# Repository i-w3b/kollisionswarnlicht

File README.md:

### kollisionswarnlicht

| Part   | Datenblatt | Preis |
|:---------------:|:---------------:|:---------------:|
|[Controller(Atmega32U4AU)](https://www.digikey.de/product-detail/de/microchip-technology/ATMEGA32U4-AU/ATMEGA32U4-AU-ND/1914602)| [Datenblatt](https://ww1.microchip.com/downloads/en/DeviceDoc/Atmel-7766-8-bit-AVR-ATmega16U4-32U4_Datasheet.pdf)  | €3,81 |
| [USB-Anschluss](https://www.digikey.de/product-detail/de/gct/USB3075-30-A/2073-USB3075-30-ACT-ND/9859705)| - | €0,55 | 
| [RJ12-Anschluss](https://www.digikey.de/product-detail/de/pulse-electronics-network/E5566-Q0LK22-L/553-2258-ND/1785239) | - | €0,45 |
| [Quartz - Alt](https://www.digikey.de/product-detail/de/txc-corporation/7A-16.000MAAJ-T/887-1086-2-ND/2118770) | - | €0,31 |
| [Quartz](https://www.digikey.de/product-detail/de/epson/FA-238-16-0000MB-C3/SER3686CT-ND/2403459) | - | €0,27 |
| [LED](https://www.digikey.de/product-detail/de/cree-inc/XHP50A-00-0000-0D0BJ40E2/XHP50A-00-0000-0D0BJ40E2TR-ND/5303071) | [Datenblatt](https://cree-led.com/media/documents/ds-XHP50.pdf) | €4,53 |
| [LED-Treiber](https://www.digikey.de/product-detail/de/leddynamics-inc/3021-D-E-1000/788-1107-ND/3114438) | [Datenblatt](http://www.leddynamics.com/wp-content/uploads/2018/11/03021_03023_BuckPuck_v3-1.pdf)| €7,83 |
| [PNP-Transistor](https://www.digikey.de/product-detail/de/taiwan-semiconductor-corporation/MMBT3906-RFG/MMBT3906RFGCT-ND/7644317) | [Datenblatt](https://www.taiwansemi.com/assets/uploads/datasheet/MMBT3906_H2001.pdf) | €0,03 |
| [Load-Switch](https://www.digikey.de/product-detail/de/infineon-technologies/BTS71202EPAXUMA1/BTS71202EPAXUMA1CT-ND/9906589) | [Datenblatt](https://www.infineon.com/dgdl/Infineon-BTS7120-2EPA-DS-v01_00-EN.pdf?fileId=5546d462636cc8fb016421dc08d31138) | 1,41€ |
| [220uF Kondensator](https://www.digikey.de/products/de?keywords=P124108CT-ND) | [Datenblatt](https://industrial.panasonic.com/cdbs/www-data/pdf/RDD0000/RDD0000C1244.pdf) |2,61€ |
| [Poti](https://www.digikey.de/product-detail/de/nidec-copal-electronics/ST32ETA502/ST32ETA502CT-ND/738477) | [Datenblatt](https://www.nidec-copal-electronics.com/e/catalog/trimmer/st-32.pdf) | 1,09€ |

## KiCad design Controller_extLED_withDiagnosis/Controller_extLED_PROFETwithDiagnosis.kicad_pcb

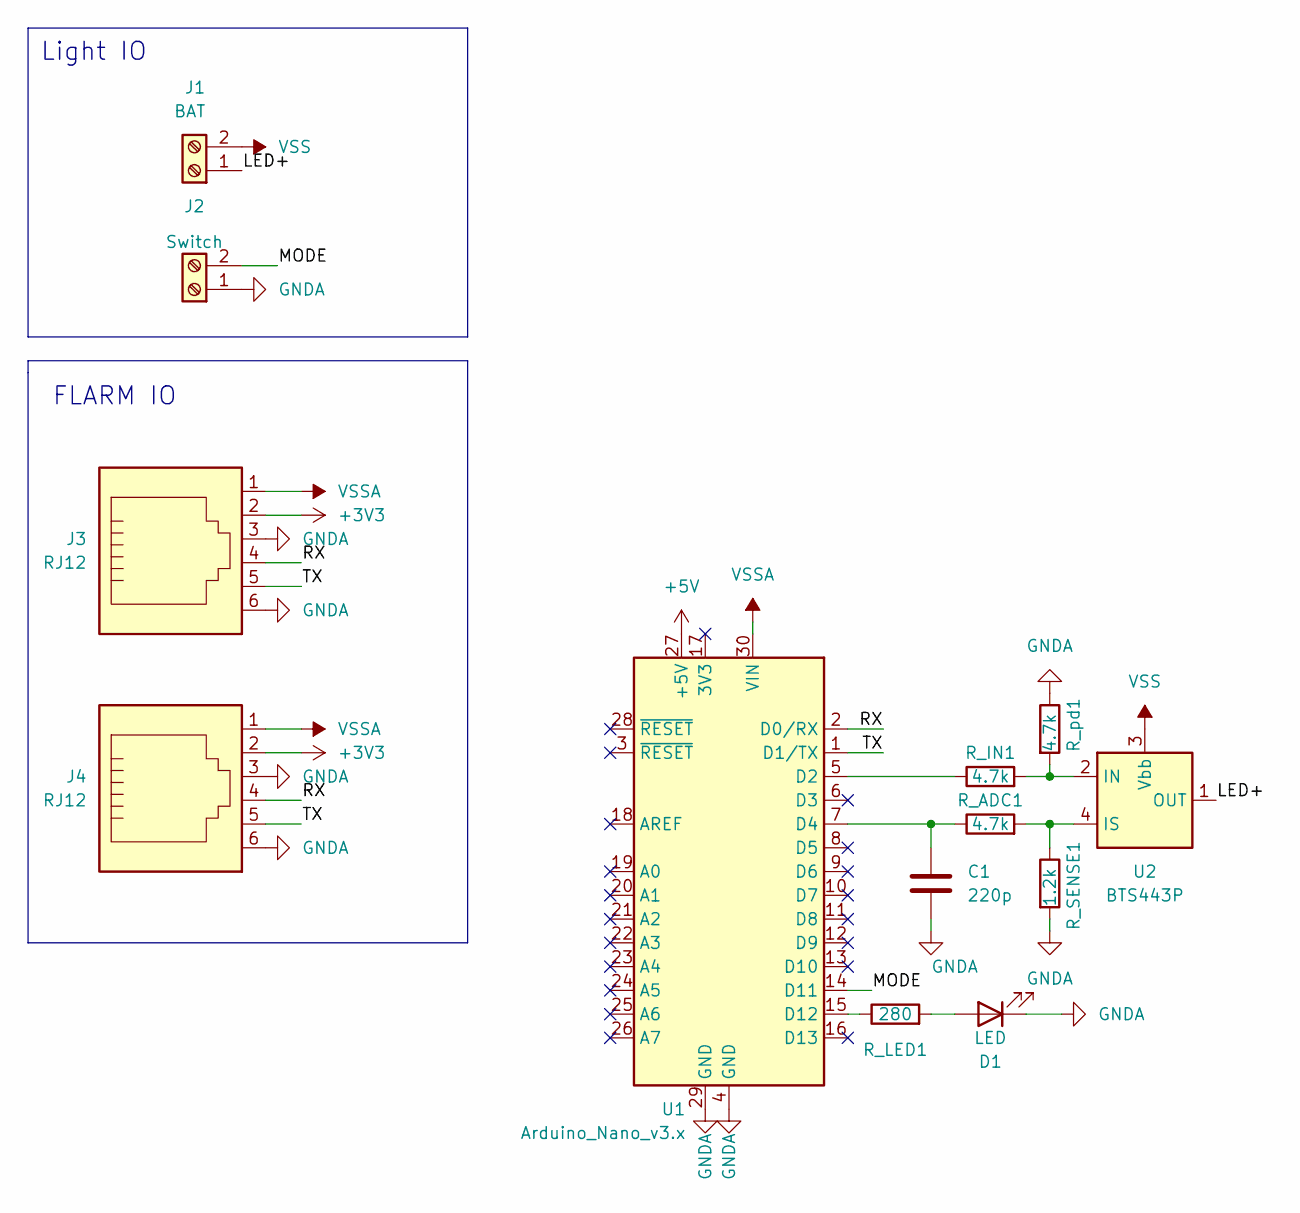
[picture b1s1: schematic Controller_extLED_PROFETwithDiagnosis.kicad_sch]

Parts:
C1: 220p; C_0805_2012Metric_Pad1.18x1.45mm_HandSolder
D1: LED; LED_D3.0mm
J1: BAT; TerminalBlock_bornier-2_P5.08mm
J2: Switch; TerminalBlock_TE_282834-2_1x02_P2.54mm_Horizontal
J3, J4: RJ12; RJ12_Amphenol_54601
R_ADC1: 4.7k; R_0805_2012Metric_Pad1.20x1.40mm_HandSolder
R_IN1: 4.7k; R_0805_2012Metric_Pad1.20x1.40mm_HandSolder
R_LED1: 280; R_0805_2012Metric_Pad1.20x1.40mm_HandSolder
R_SENSE1: 1.2k; R_0805_2012Metric_Pad1.20x1.40mm_HandSolder
R_pd1: 4.7k; R_0805_2012Metric_Pad1.20x1.40mm_HandSolder
U1: Arduino_Nano_v3.x; Arduino_Nano
U2: BTS443P; TO-252-4

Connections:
+3V3: J3.2, J4.2
+5V: U1.27 (+5V)
/LED+: J1.1, U2.1 (OUT), U2.5 (OUT)
/MODE: J2.2, U1.14 (D11)
/RX: J3.4, J4.4, U1.2 (D0/RX)
/TX: J3.5, J4.5, U1.1 (D1/TX)
GNDA: C1.2, D1.1 (K), J2.1, J3.3, J3.6, J4.3, J4.6, R_SENSE1.2, R_pd1.1, U1.4 (GND), U1.29 (GND)
unnamed: C1.1, R_ADC1.1, U1.7 (D4)
unnamed: D1.2 (A), R_LED1.2
unnamed: R_ADC1.2, R_SENSE1.1, U2.4 (IS)
unnamed: R_IN1.2, R_pd1.2, U2.2 (IN)
unnamed: R_LED1.1, U1.15 (D12)
unnamed: R_IN1.1, U1.5 (D2)
VSS: J1.2, U2.3 (Vbb)
VSSA: J3.1, J4.1, U1.30 (VIN)

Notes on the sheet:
Light IO
FLARM IO

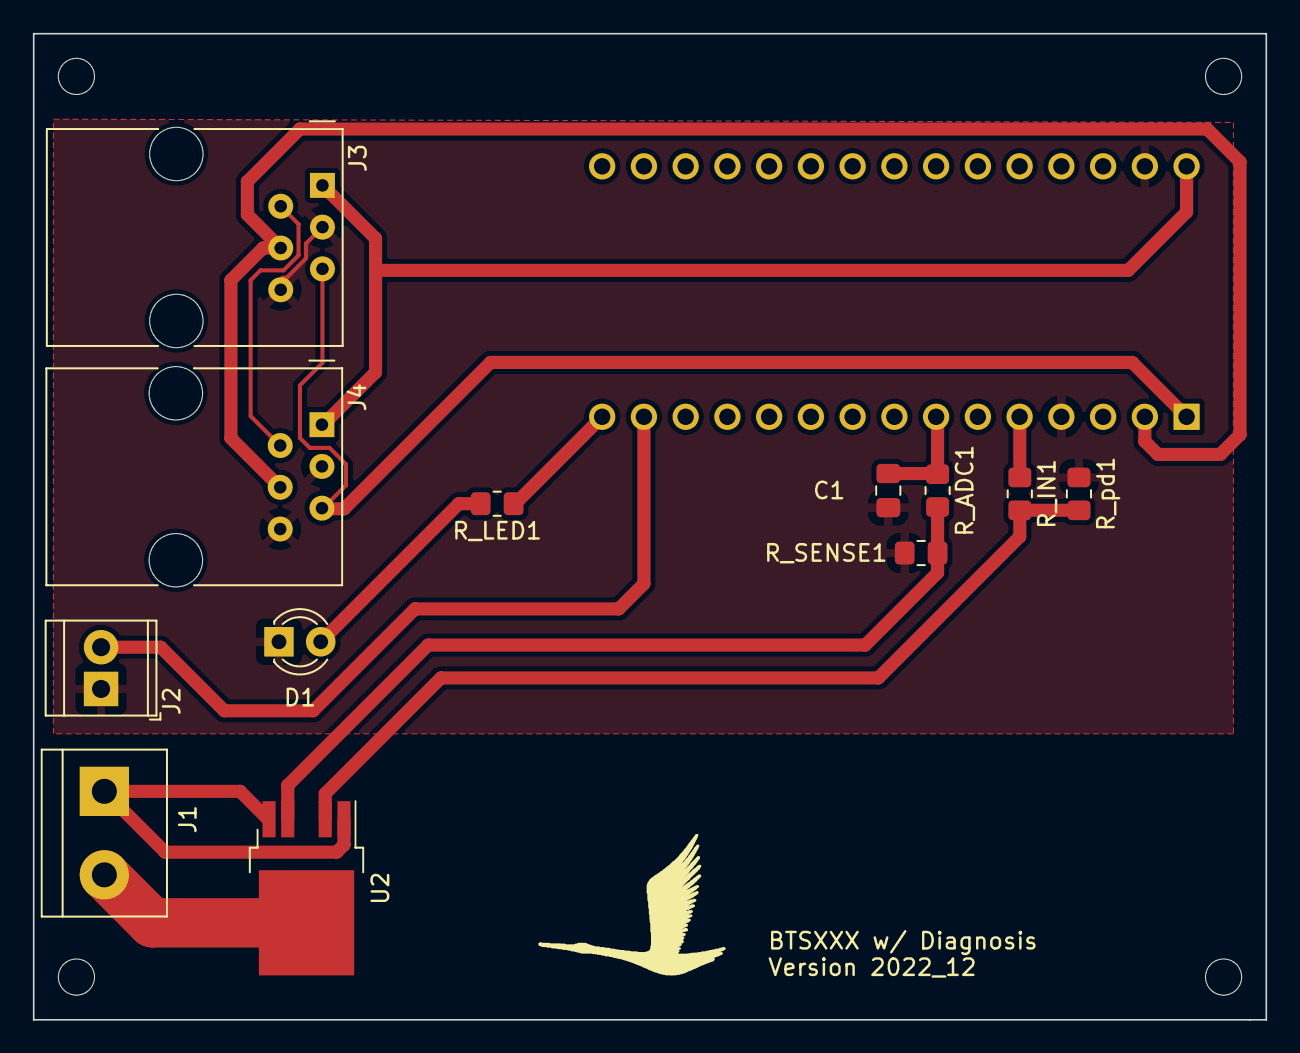
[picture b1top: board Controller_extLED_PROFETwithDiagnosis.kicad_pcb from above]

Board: 2 copper layers, 75.0 x 60.0 mm, 13 parts (1 on the bottom side), 14 nets.

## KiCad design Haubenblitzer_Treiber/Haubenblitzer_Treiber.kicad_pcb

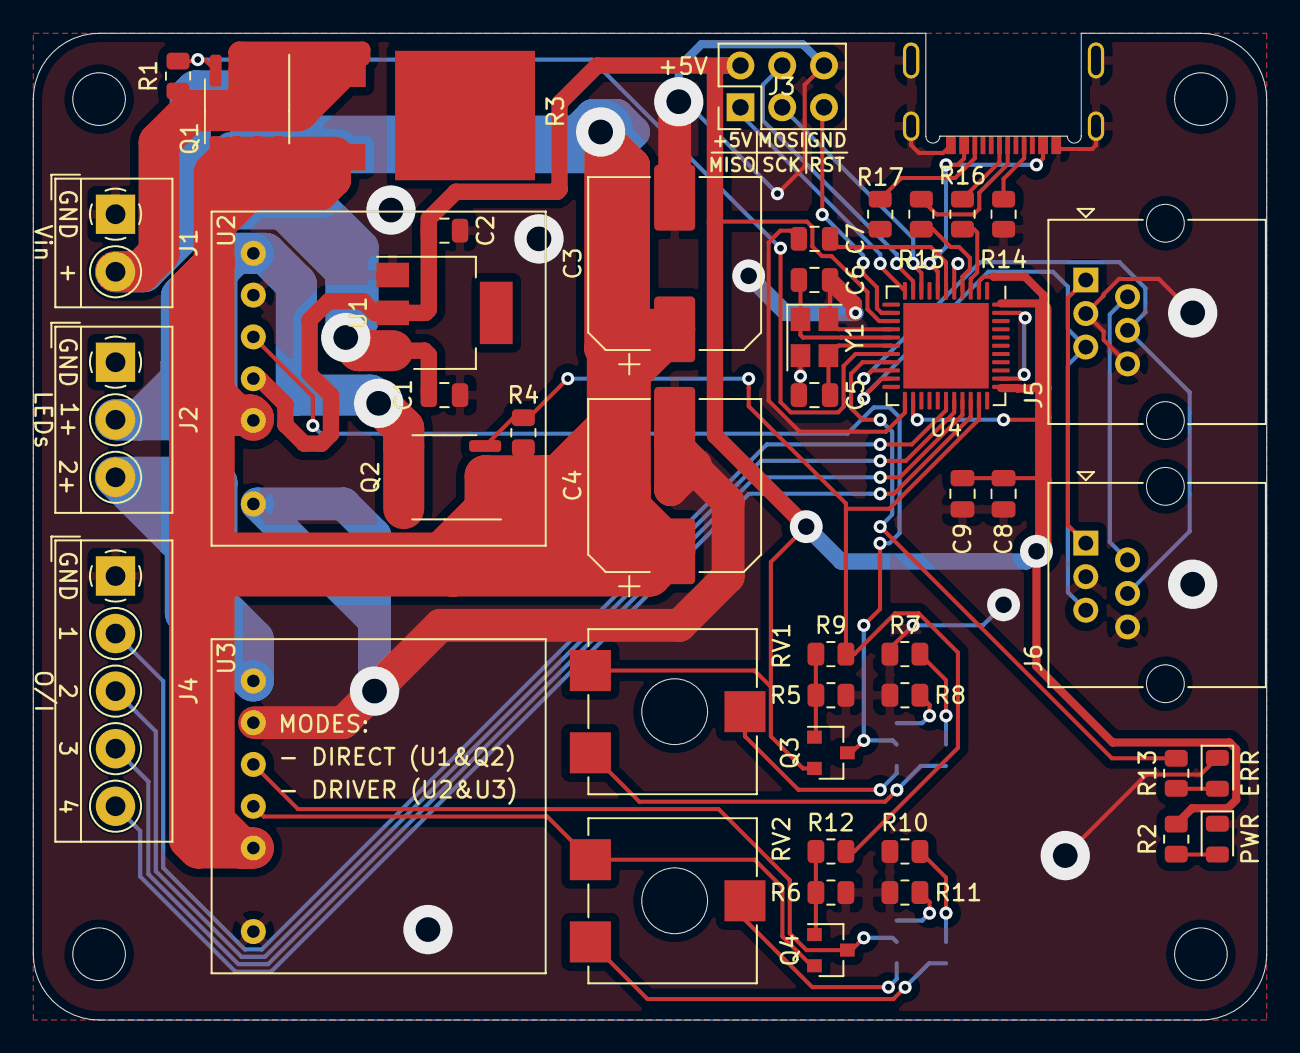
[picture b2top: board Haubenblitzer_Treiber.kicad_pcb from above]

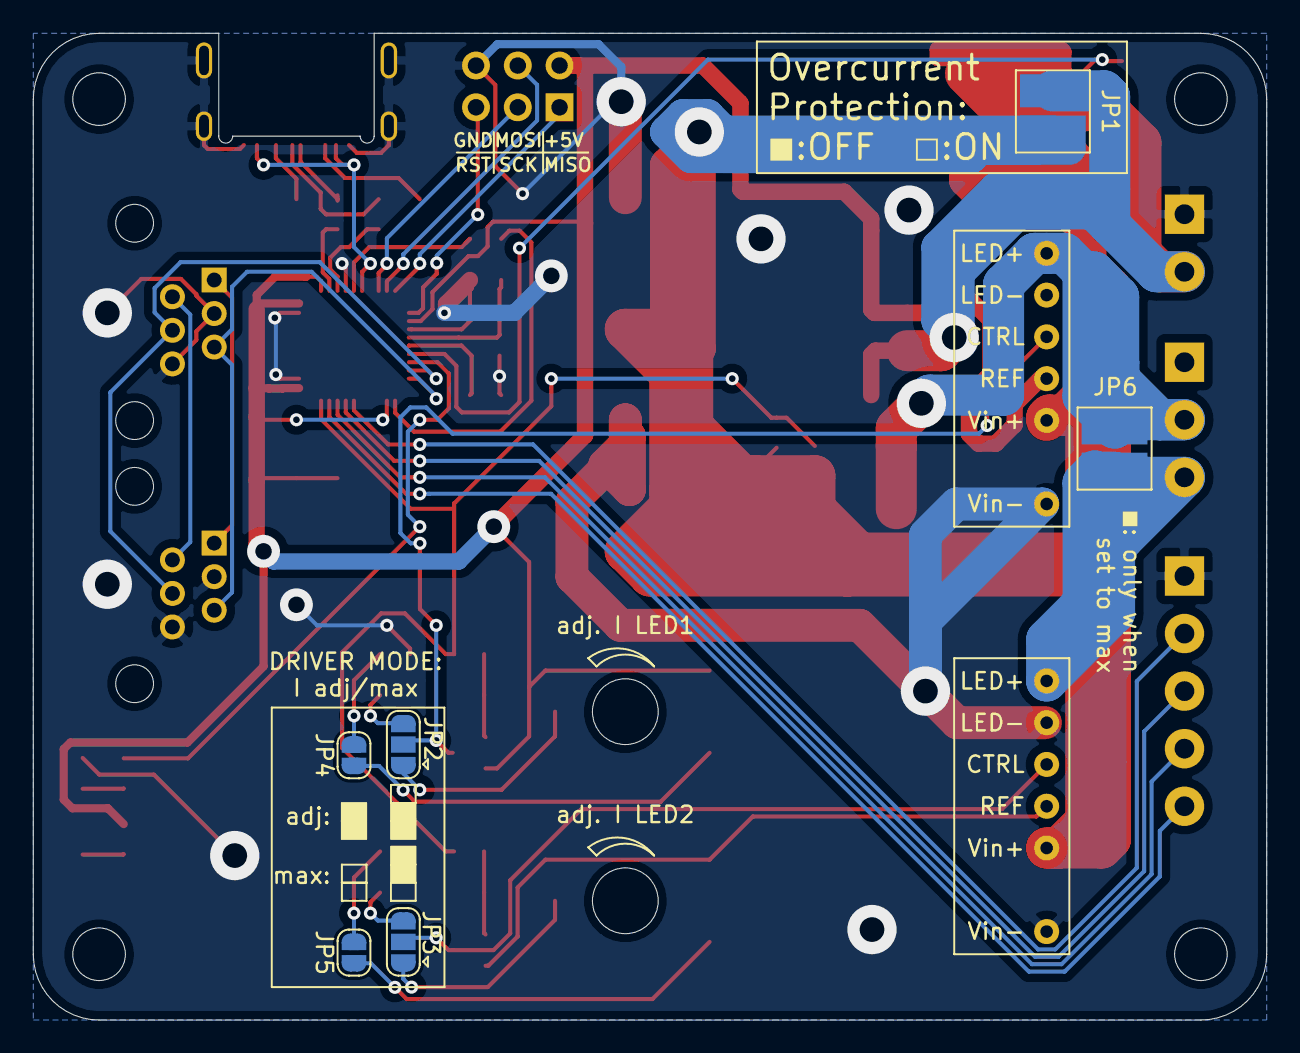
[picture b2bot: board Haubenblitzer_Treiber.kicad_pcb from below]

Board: 2 copper layers, 75.0 x 60.0 mm, 56 parts (6 on the bottom side), 46 nets.

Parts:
C1, C7: 1uF; C_0805_2012Metric
C2: 4.7uF; C_0805_2012Metric
C3, C4: 220uF; CP_Elec_10x10
C5, C6: 18pF; C_0805_2012Metric
C8: 0.1uF; C_0805_2012Metric
C9: 10uF; C_0805_2012Metric
ERR: LED; LED_0805_2012Metric
H1, H2, H3, H4: MountingHole; MountingHole_3.2mm_M3
J1: Screw_Terminal; TerminalBlock_4Ucon_1x02_P3.50mm_Horizontal
J2: Screw_Terminal; TerminalBlock_4Ucon_1x03_P3.50mm_Horizontal
J3: ISCP; PinHeader_2x03_P2.54mm_Vertical
J4: Screw_Terminal; TerminalBlock_4Ucon_1x05_P3.50mm_Horizontal
J5, J6: RJ12; RJ25_Wayconn_MJEA-660X1_Horizontal
J7: USB_C_4510
JP1, JP6: Jumper; SolderJumper-2_P1.3mm_Open_Pad2.0x4.0mm
JP2, JP3: Jumper; SolderJumper-3_P1.3mm_Open_RoundedPad1.0x1.5mm
JP4, JP5: Jumper; SolderJumper-2_P1.3mm_Open_RoundedPad1.0x1.5mm
PWR: LED; LED_0805_2012Metric
Q1, Q2: IRF7205; SOIC-8_IRF7205
Q3, Q4: AO3401A; SOT-23
R1, R4: 10k; R_0805_2012Metric
R2, R13: 220; R_0805_2012Metric
R3: 5; PAK-2
R5, R6: 200; R_0805_2012Metric
R7, R11: 5K; R_0805_2012Metric
R8, R9, R12: 5k; R_0805_2012Metric
R10: 1K; R_0805_2012Metric
R14, R17: 5.1K; R_0805_2012Metric
R15, R16: 22; R_0805_2012Metric
RV1, RV2: R_POT; Potentiometer_ACP_PS10_Vertical_Hole
U1: LDL1117S50R; SOT-223
U2, U3: 3021-D-E-1000
U4: ATmega16U4-AU; QFN-44-1EP_7x7mm_P0.5mm_EP5.2x5.2mm
Y1: Crystal; Crystal_SMD_3225-4Pin_3.2x2.5mm

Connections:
+5V: C2.2, C8.2, C9.2, J3.2, Q3.2, R2.1, RV1.3, U1.2, U2.4, U4.2, U4.14, U4.24, U4.34, U4.44
/CLK_1: C5.2, U4.17, Y1.3
/CLK_2: C6.2, U4.16, Y1.1
/D+: R15.2, U4.4
/D-: R16.2, U4.3
/IO_BRIDGE_INRUSH_R: Q1.2, R1.2, U4.18
/IO_LED: Q2.2, R4.2, R5.1, R6.1, U4.32
/IO_MISC1: J4.2, U4.28
/IO_MISC2: J4.3, U4.29
/IO_MISC3: J4.4, U4.30
/IO_MISC4: J4.5, U4.31
/LED1_CTRL: JP2.2, Q3.3, U2.3
/LED2_CTRL: JP3.2, Q4.3, U3.3
/LED2_REF: Q4.2, RV2.3, U3.4
/MISO: J3.1, U4.11
/MOSI: J3.4, U4.10
/RESET: J3.5, U4.13
/RJ12_V1: J5.1, J6.1
/RJ12_V2: J5.2, J6.2
/RX: J5.4, J6.4, U4.20
/SCK: J3.3, U4.9
/TX: J5.5, J6.5, U4.21
/U_Driver: C3.1, C4.1, JP1.2, Q1.1, Q2.3, R3.2, R4.1, U2.5, U3.5
/U_LED1: J2.2, JP6.1, Q2.1, U2.1
/U_LED2: J2.3, JP6.2, U3.1
GND: C1.1, C2.1, C3.2, C4.2, C5.1, C6.1, C7.1, C8.1, C9.1, ERR.1, J1.1, J3.6, J4.1, J5.3, J5.6, J6.3, J6.6, J7.A1, J7.A12, J7.B1, J7.B12, J7.GND, PWR.1, R7.2, R8.2, R9.2, R10.2, R11.2, R12.2, R14.2, R17.2, U1.1, U2.2, U2.6, U3.2, U3.6, U4.5, U4.15, U4.23, U4.35, U4.43, Y1.2, Y1.4
unnamed: C7.2, U4.6
unnamed: PWR.2, R2.2
unnamed: ERR.2, R13.2
unnamed: J7.A5, R14.1
unnamed: J7.A6, R15.1
unnamed: J7.A7, R16.1
unnamed: J7.B5, R17.1
unnamed: JP2.1, RV1.2
unnamed: JP2.3, R8.1
unnamed: JP3.1, RV2.2
unnamed: JP3.3, R11.1
unnamed: JP4.1, RV1.1
unnamed: JP4.2, R7.1
unnamed: JP5.1, RV2.1
unnamed: JP5.2, R10.1
unnamed: Q3.1, R5.2, R9.1
unnamed: Q4.1, R6.2, R12.1
unnamed: R13.1, U4.19
VBUS: J7.A4, J7.A9, J7.B4, J7.B9, U4.7
VCC: C1.2, J1.2, JP1.1, Q1.3, R1.1, R3.1, U1.3

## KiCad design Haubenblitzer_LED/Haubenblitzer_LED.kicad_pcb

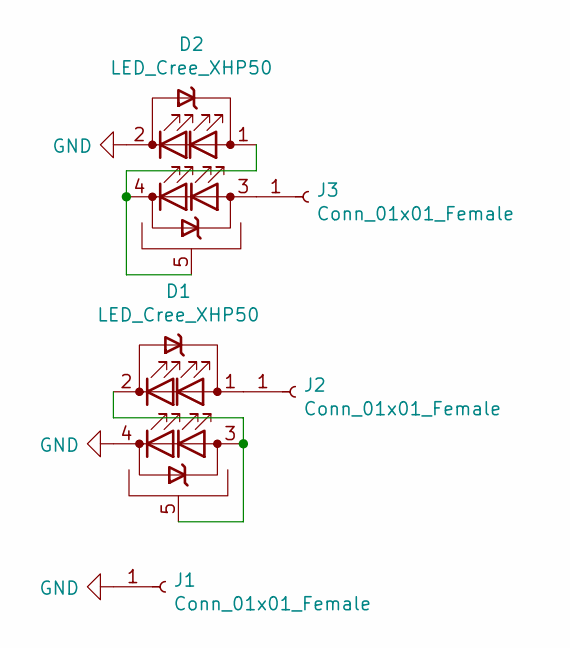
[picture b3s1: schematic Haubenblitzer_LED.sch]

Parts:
D1, D2: LED_Cree_XHP50; LED_Cree-XHP50
J1: Conn_01x01_Female; SolderWire-0.5sqmm_1x01_D0.9mm_OD2.3mm
J2, J3: Conn_01x01_Female; SolderWirePad_1x01_SMD_2.5x5mm

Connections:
GND: D1.4 (K), D2.2 (K), J1.1
unnamed: D1.1 (A), J2.1
unnamed: D1.2 (K), D1.3 (A), D1.5 (PAD)
unnamed: D2.1 (A), D2.4 (K), D2.5 (PAD)
unnamed: D2.3 (A), J3.1

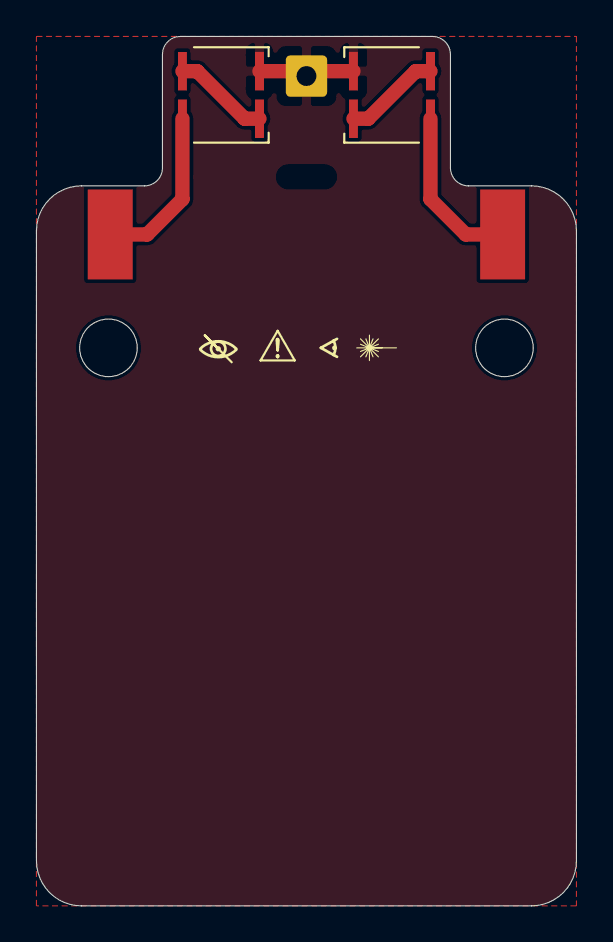
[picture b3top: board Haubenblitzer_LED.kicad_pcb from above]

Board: 2 copper layers, 30.0 x 48.3 mm, 5 parts (0 on the bottom side), 5 nets.

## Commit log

2021-07-13 updated transistor, added Load-Switch, Poti
2021-08-17 added ESD protection and gerber files
2021-08-17 added ESD protection to USB port and gerber files
2021-08-17 cleanup + added gerber files
2021-08-17 updated LED footprint
2022-06-09 Version2.0
2022-12-16 version 0
2022-12-17 comprehensive renaming
2022-12-17 Controller for old Profet versions added
2022-12-17 add some more documentation
2022-12-17 Logos added
2022-12-17 gitignore added
2022-12-17 renaming Jens design
2022-12-17 shorter naming
2022-12-17 moved J2 on Silkscreen
2022-12-17 meved pull-up
2022-12-17 larger groundplane
2022-12-17 accidentally added backups
2022-12-18 moved project file
2022-12-18 updated logo and silkscreen
2022-12-18 updated logo
2022-12-18 DRC weirness
